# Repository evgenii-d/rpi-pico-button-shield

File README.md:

# Raspberry Pi Pico Button Shield

KiCad design files for a simple shield for the Raspberry Pi Pico.
The shield is designed to easily break out most of the Pico's GPIO pins
to multiple 2-pin 2.54mm pitch male headers.
This makes it convenient for connecting external components like buttons,
switches, LEDs, or sensors using standard Dupont wires.
Ideal for prototyping or creating simple custom interfaces.

## Features

* Directly fits onto a Pico or Pico W (requires headers soldered on the Pico).
* Breaks out most Pico pins into pairs on standard 2.54mm pitch male headers.
* Includes four 2.7mm mounting holes.
* Simple PCB design (requires only through-hole headers to be soldered).

## Usage

This example demonstrates reading multiple buttons connected to the shield
using the [SimpleButton][1] module on [MicroPython][2].

```python
import sys
from utime import sleep_ms
from machine import Pin
from simple_button import SimpleButton

def echo(message: str) -> None:
    sys.stdout.write(f"{message} \n")

def main() -> None:
    gpio = list(range(23))
    buttons: list[SimpleButton] = []

    for index, gpio_pin in enumerate(gpio):
        buttons.append(
            SimpleButton(
                gpio_pin,
                press_callback=lambda i=index: echo(f"Button {i} pressed"),
                release_callback=lambda i=index: echo(f"Button {i} released"),
                pull=Pin.PULL_UP,
                active_low=True
            )
        )

    while True:
        # Do other things or just sleep
        sleep_ms(500)

if __name__ == "__main__":
    main()

```

[1]: https://github.com/evgenii-d/micropython-simple-button
[2]: https://docs.micropython.org/en/latest/rp2/quickref.html

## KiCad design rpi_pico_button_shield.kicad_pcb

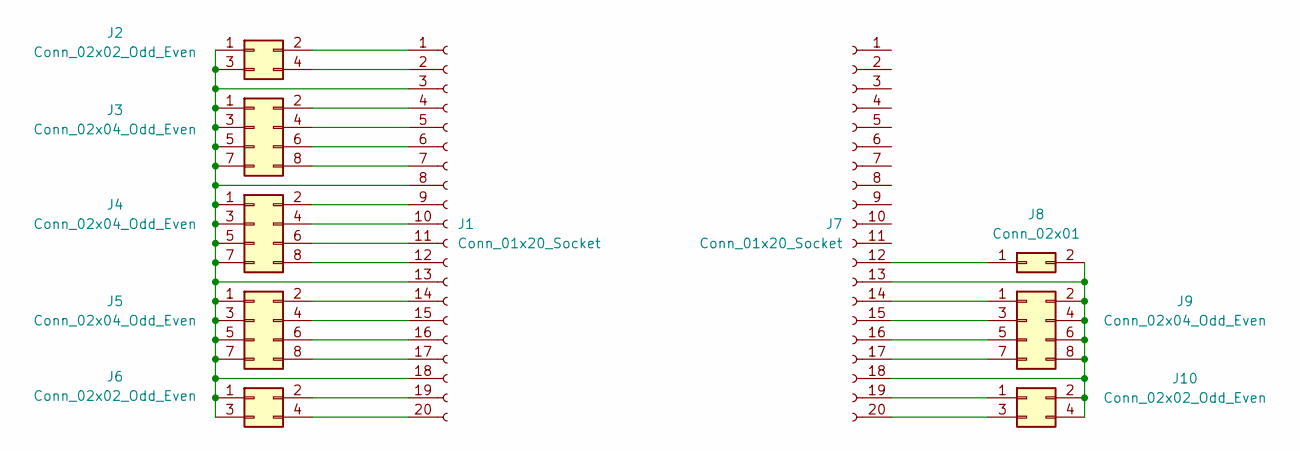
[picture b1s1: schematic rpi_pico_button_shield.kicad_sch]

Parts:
J1, J7: Conn_01x20_Socket; PinSocket_1x20_P2.54mm_Vertical
J2, J6, J10: Conn_02x02_Odd_Even; PinHeader_2x02_P2.54mm_Vertical
J3, J4, J5, J9: Conn_02x04_Odd_Even; PinHeader_2x04_P2.54mm_Vertical
J8: Conn_02x01; PinHeader_2x01_P2.54mm_Vertical

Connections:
unnamed: J1.1, J2.2
unnamed: J1.2, J2.4
unnamed: J1.4, J3.2
unnamed: J1.5, J3.4
unnamed: J1.6, J3.6
unnamed: J1.7, J3.8
unnamed: J1.9, J4.2
unnamed: J1.10, J4.4
unnamed: J1.11, J4.6
unnamed: J1.12, J4.8
unnamed: J1.3, J1.8, J1.13, J1.18, J2.1, J2.3, J3.1, J3.3, J3.5, J3.7, J4.1, J4.3, J4.5, J4.7, J5.1, J5.3, J5.5, J5.7, J6.1, J6.3
unnamed: J1.14, J5.2
unnamed: J1.15, J5.4
unnamed: J1.16, J5.6
unnamed: J1.17, J5.8
unnamed: J1.19, J6.2
unnamed: J1.20, J6.4
unnamed: J7.12, J8.1
unnamed: J7.14, J9.1
unnamed: J7.15, J9.3
unnamed: J7.16, J9.5
unnamed: J7.17, J9.7
unnamed: J7.19, J10.1
unnamed: J7.13, J7.18, J8.2, J9.2, J9.4, J9.6, J9.8, J10.2, J10.4
unnamed: J7.20, J10.3

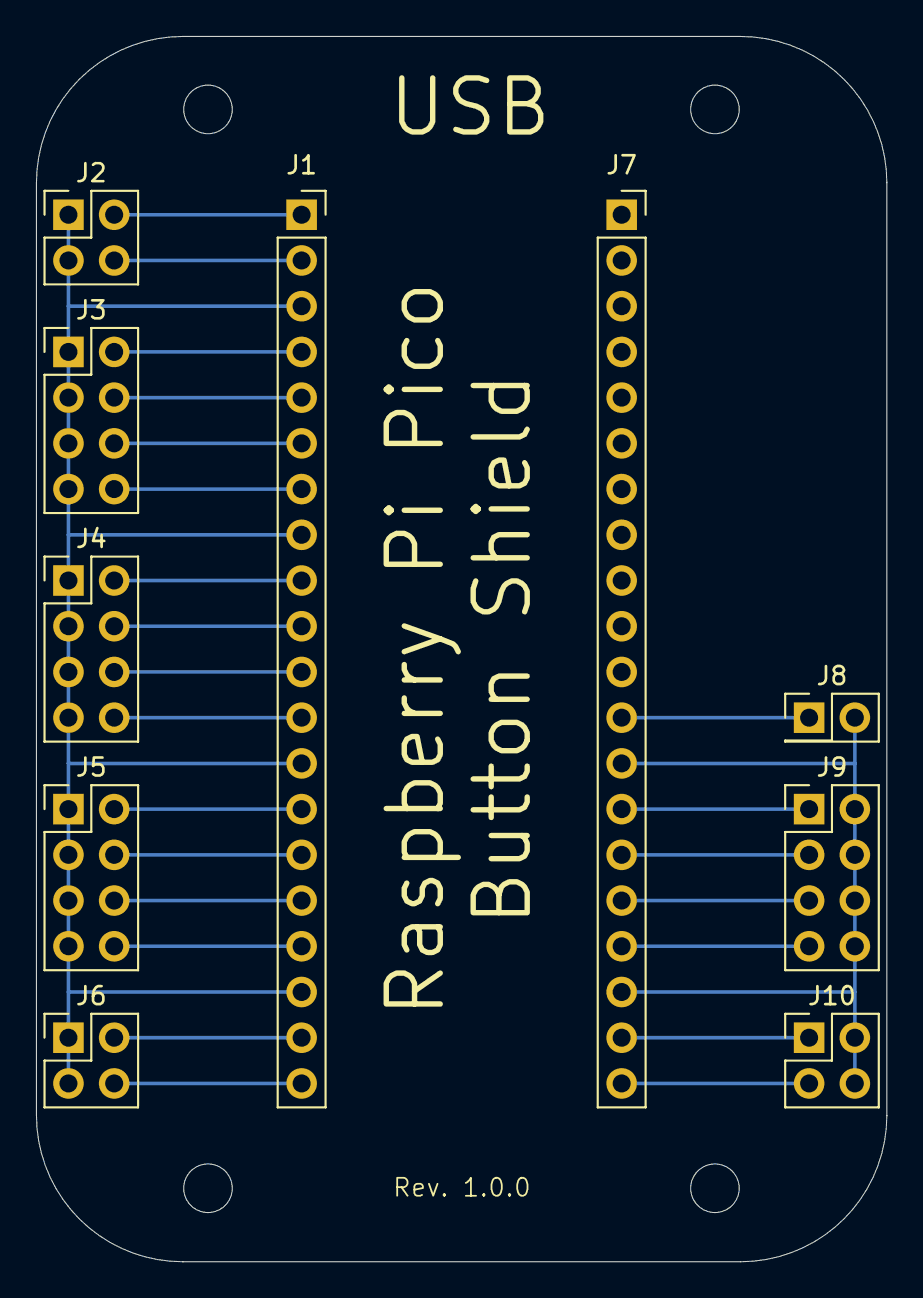
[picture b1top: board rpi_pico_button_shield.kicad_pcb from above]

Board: 2 copper layers, 47.2 x 68.1 mm, 10 parts (0 on the bottom side), 25 nets.

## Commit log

2025-03-12 chore: add pcb photo
2025-03-12 chore: fix typo
2025-03-30 chore: update README.md, add usage example
